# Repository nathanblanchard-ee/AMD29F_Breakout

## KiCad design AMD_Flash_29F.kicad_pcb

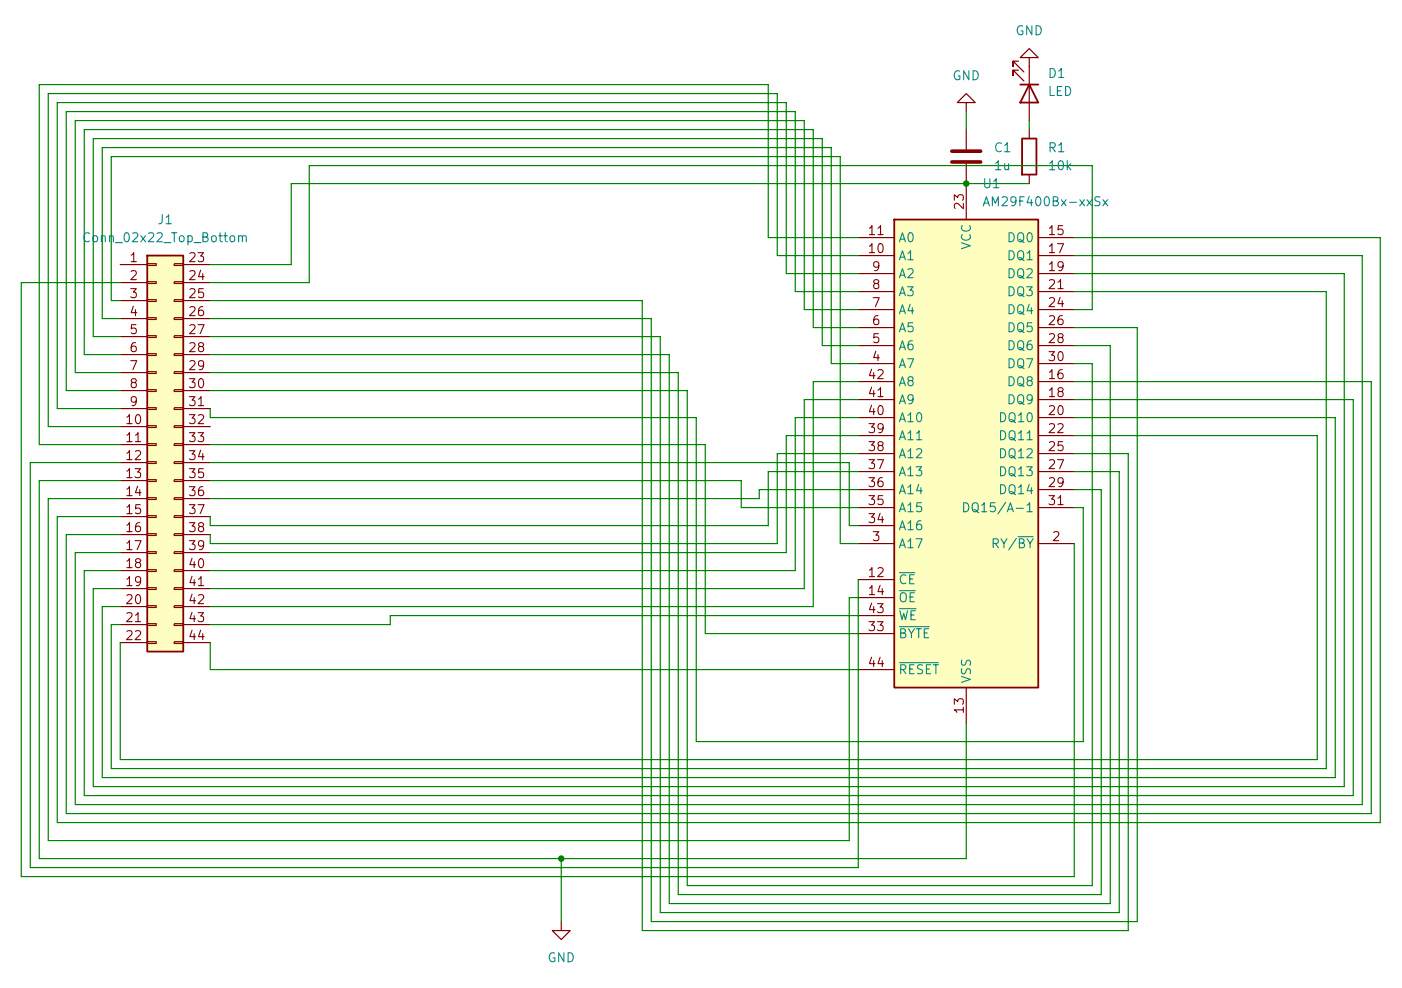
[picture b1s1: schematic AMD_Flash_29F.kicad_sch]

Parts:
C1: 1u; C_0603_1608Metric
D1: LED; LED_0603_1608Metric
J1: Conn_02x22_Top_Bottom; PinHeader_2x22_P2.54mm_Vertical
R1: 10k; R_0603_1608Metric
U1: AM29F400Bx-xxSx; SOP-44_13.3x28.2mm_P1.27mm

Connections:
GND: C1.1, D1.1 (K), J1.13, U1.13 (VSS), U1.32 (VSS)
unnamed: D1.2 (A), R1.1
unnamed: J1.2, U1.2 (RY/~BY)
unnamed: J1.3, U1.3 (A17)
unnamed: J1.4, U1.4 (A7)
unnamed: J1.5, U1.5 (A6)
unnamed: J1.6, U1.6 (A5)
unnamed: J1.7, U1.7 (A4)
unnamed: J1.8, U1.8 (A3)
unnamed: J1.9, U1.9 (A2)
unnamed: J1.10, U1.10 (A1)
unnamed: J1.11, U1.11 (A0)
unnamed: J1.12, U1.12 (~CE)
unnamed: J1.14, U1.14 (~OE)
unnamed: J1.15, U1.15 (DQ0)
unnamed: J1.16, U1.16 (DQ8)
unnamed: J1.17, U1.17 (DQ1)
unnamed: J1.18, U1.18 (DQ9)
unnamed: J1.19, U1.19 (DQ2)
unnamed: J1.20, U1.20 (DQ10)
unnamed: J1.21, U1.21 (DQ3)
unnamed: J1.22, U1.22 (DQ11)
unnamed: C1.2, J1.23, R1.2, U1.23 (VCC)
unnamed: J1.24, U1.24 (DQ4)
unnamed: J1.25, U1.25 (DQ12)
unnamed: J1.26, U1.26 (DQ5)
unnamed: J1.27, U1.27 (DQ13)
unnamed: J1.28, U1.28 (DQ6)
unnamed: J1.29, U1.29 (DQ14)
unnamed: J1.30, U1.30 (DQ7)
unnamed: J1.31, U1.31 (DQ15/A-1)
unnamed: J1.33, U1.33 (~BYTE)
unnamed: J1.34, U1.34 (A16)
unnamed: J1.35, U1.35 (A15)
unnamed: J1.36, U1.36 (A14)
unnamed: J1.37, U1.37 (A13)
unnamed: J1.38, U1.38 (A12)
unnamed: J1.39, U1.39 (A11)
unnamed: J1.40, U1.40 (A10)
unnamed: J1.41, U1.41 (A9)
unnamed: J1.42, U1.42 (A8)
unnamed: J1.43, U1.43 (~WE)
unnamed: J1.44, U1.44 (~RESET)

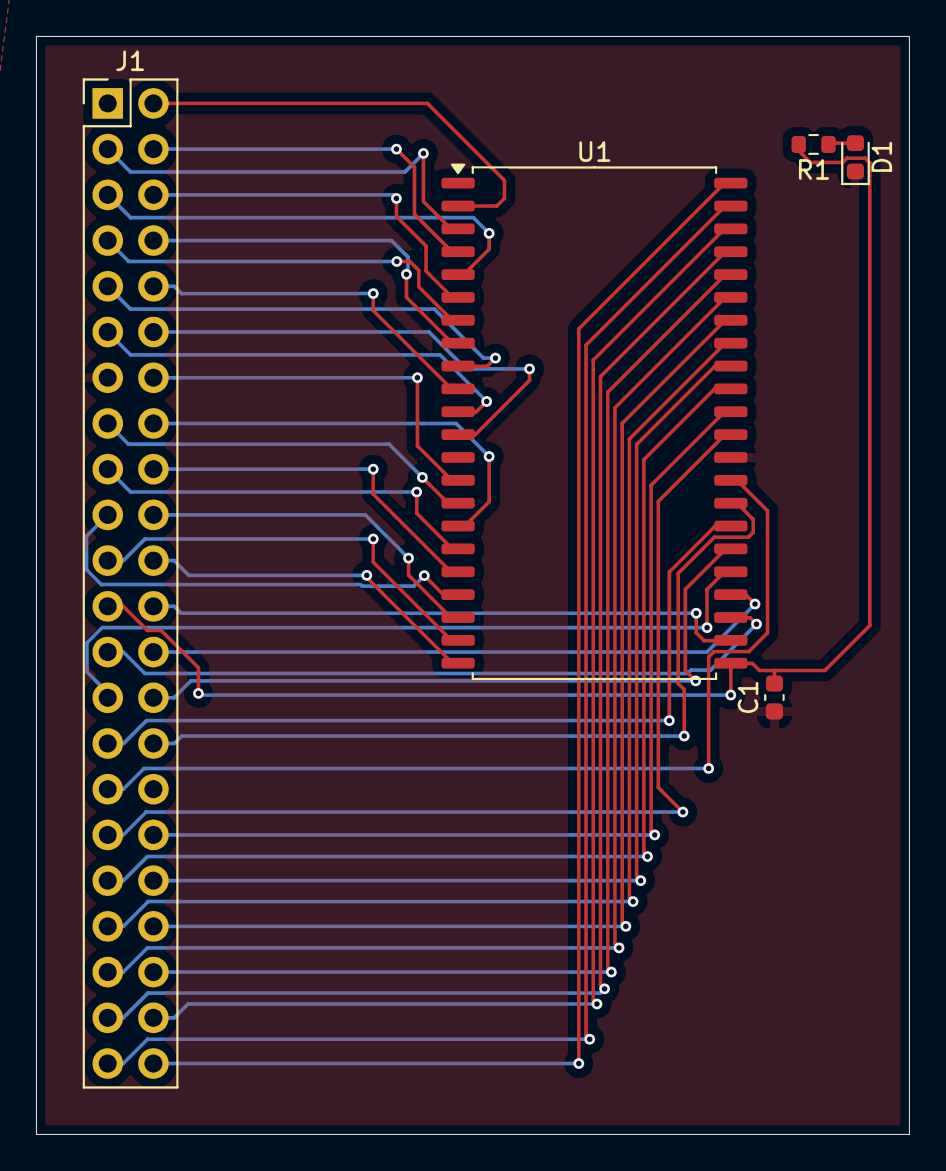
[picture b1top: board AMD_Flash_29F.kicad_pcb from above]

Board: 2 copper layers, 48.5 x 61.0 mm, 5 parts (0 on the bottom side), 43 nets.

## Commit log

2025-09-10 Add KiCAD files
